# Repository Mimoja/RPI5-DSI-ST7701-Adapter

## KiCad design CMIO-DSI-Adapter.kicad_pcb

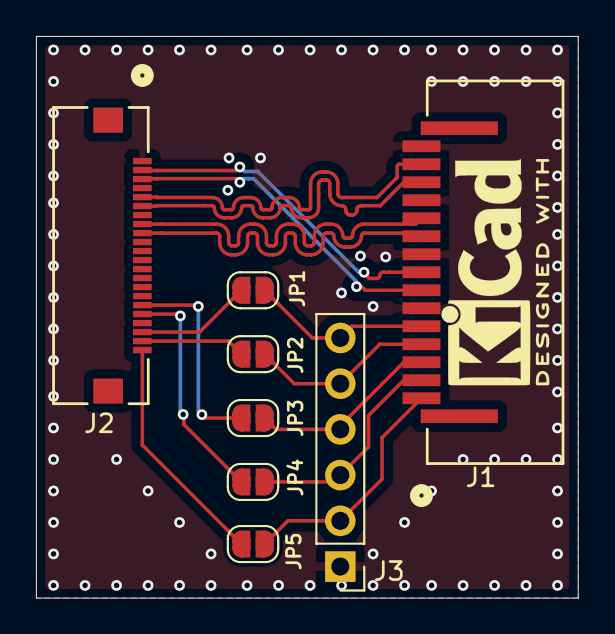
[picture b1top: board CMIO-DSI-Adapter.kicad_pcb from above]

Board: 2 copper layers, 30.1 x 31.2 mm, 8 parts (0 on the bottom side), 14 nets.

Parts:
J1: SFW15R-2STE1LF; CON15_1X15_DRB_SFW_FCI
J2: 545482271; CONN_54548-2271_MOL
J3: Conn_01x05_Pin; PinHeader_1x06_P2.54mm_Vertical
JP1: SCL; SolderJumper-2_P1.3mm_Open_RoundedPad1.0x1.5mm
JP2: SDA; SolderJumper-2_P1.3mm_Open_RoundedPad1.0x1.5mm
JP3: Reset; SolderJumper-2_P1.3mm_Open_RoundedPad1.0x1.5mm
JP4: LEDA; SolderJumper-2_P1.3mm_Open_RoundedPad1.0x1.5mm
JP5: VCC; SolderJumper-2_P1.3mm_Open_RoundedPad1.0x1.5mm

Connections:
/CAM_GPIO0: J2.17, JP3.1 (A)
/CAM_GPIO1: J2.18, JP4.1 (A)
/CLKN: J1.11, J2.8
/CLKP: J1.10, J2.9
/D0N: J1.8, J2.2
/D0P: J1.7, J2.3
/D1N: J1.14, J2.5
/D1P: J1.13, J2.6
/GND: J1.6, J1.9, J1.12, J1.15, J2.1, J2.4, J2.10, J2.13, J2.16, J2.19, J3.1
/LEDA: J1.2, J3.3, JP4.2 (B)
/RESET: J1.3, J3.4, JP3.2 (B)
/SCL: J1.5, J2.20, J3.6, JP1.1 (A), JP1.2 (B)
/SDA: J1.4, J2.21, J3.5, JP2.1 (A), JP2.2 (B)
/VCC: J1.1, J2.22, J3.2, JP5.1 (A), JP5.2 (B)

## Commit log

2024-12-23 Initial commit before review
